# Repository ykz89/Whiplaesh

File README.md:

# Whiplaesh
Inspired by Aespa's latest single '[Whiplash](https://www.youtube.com/watch?v=jWQx2f-CErU)'.

This is a 32 (23333+2) key wireless keyboard featuring:

- Nice!Nano (or alike) controller
- Hotswap or direct solder support for choc, gateron low profile, and MX switches
- Battery through holes for soldering a JST connector or direct wire
- On/off switch
- Reset switch
- VIK connector

## Case
Todo

## Build guide
Todo

## Firmware
Todo

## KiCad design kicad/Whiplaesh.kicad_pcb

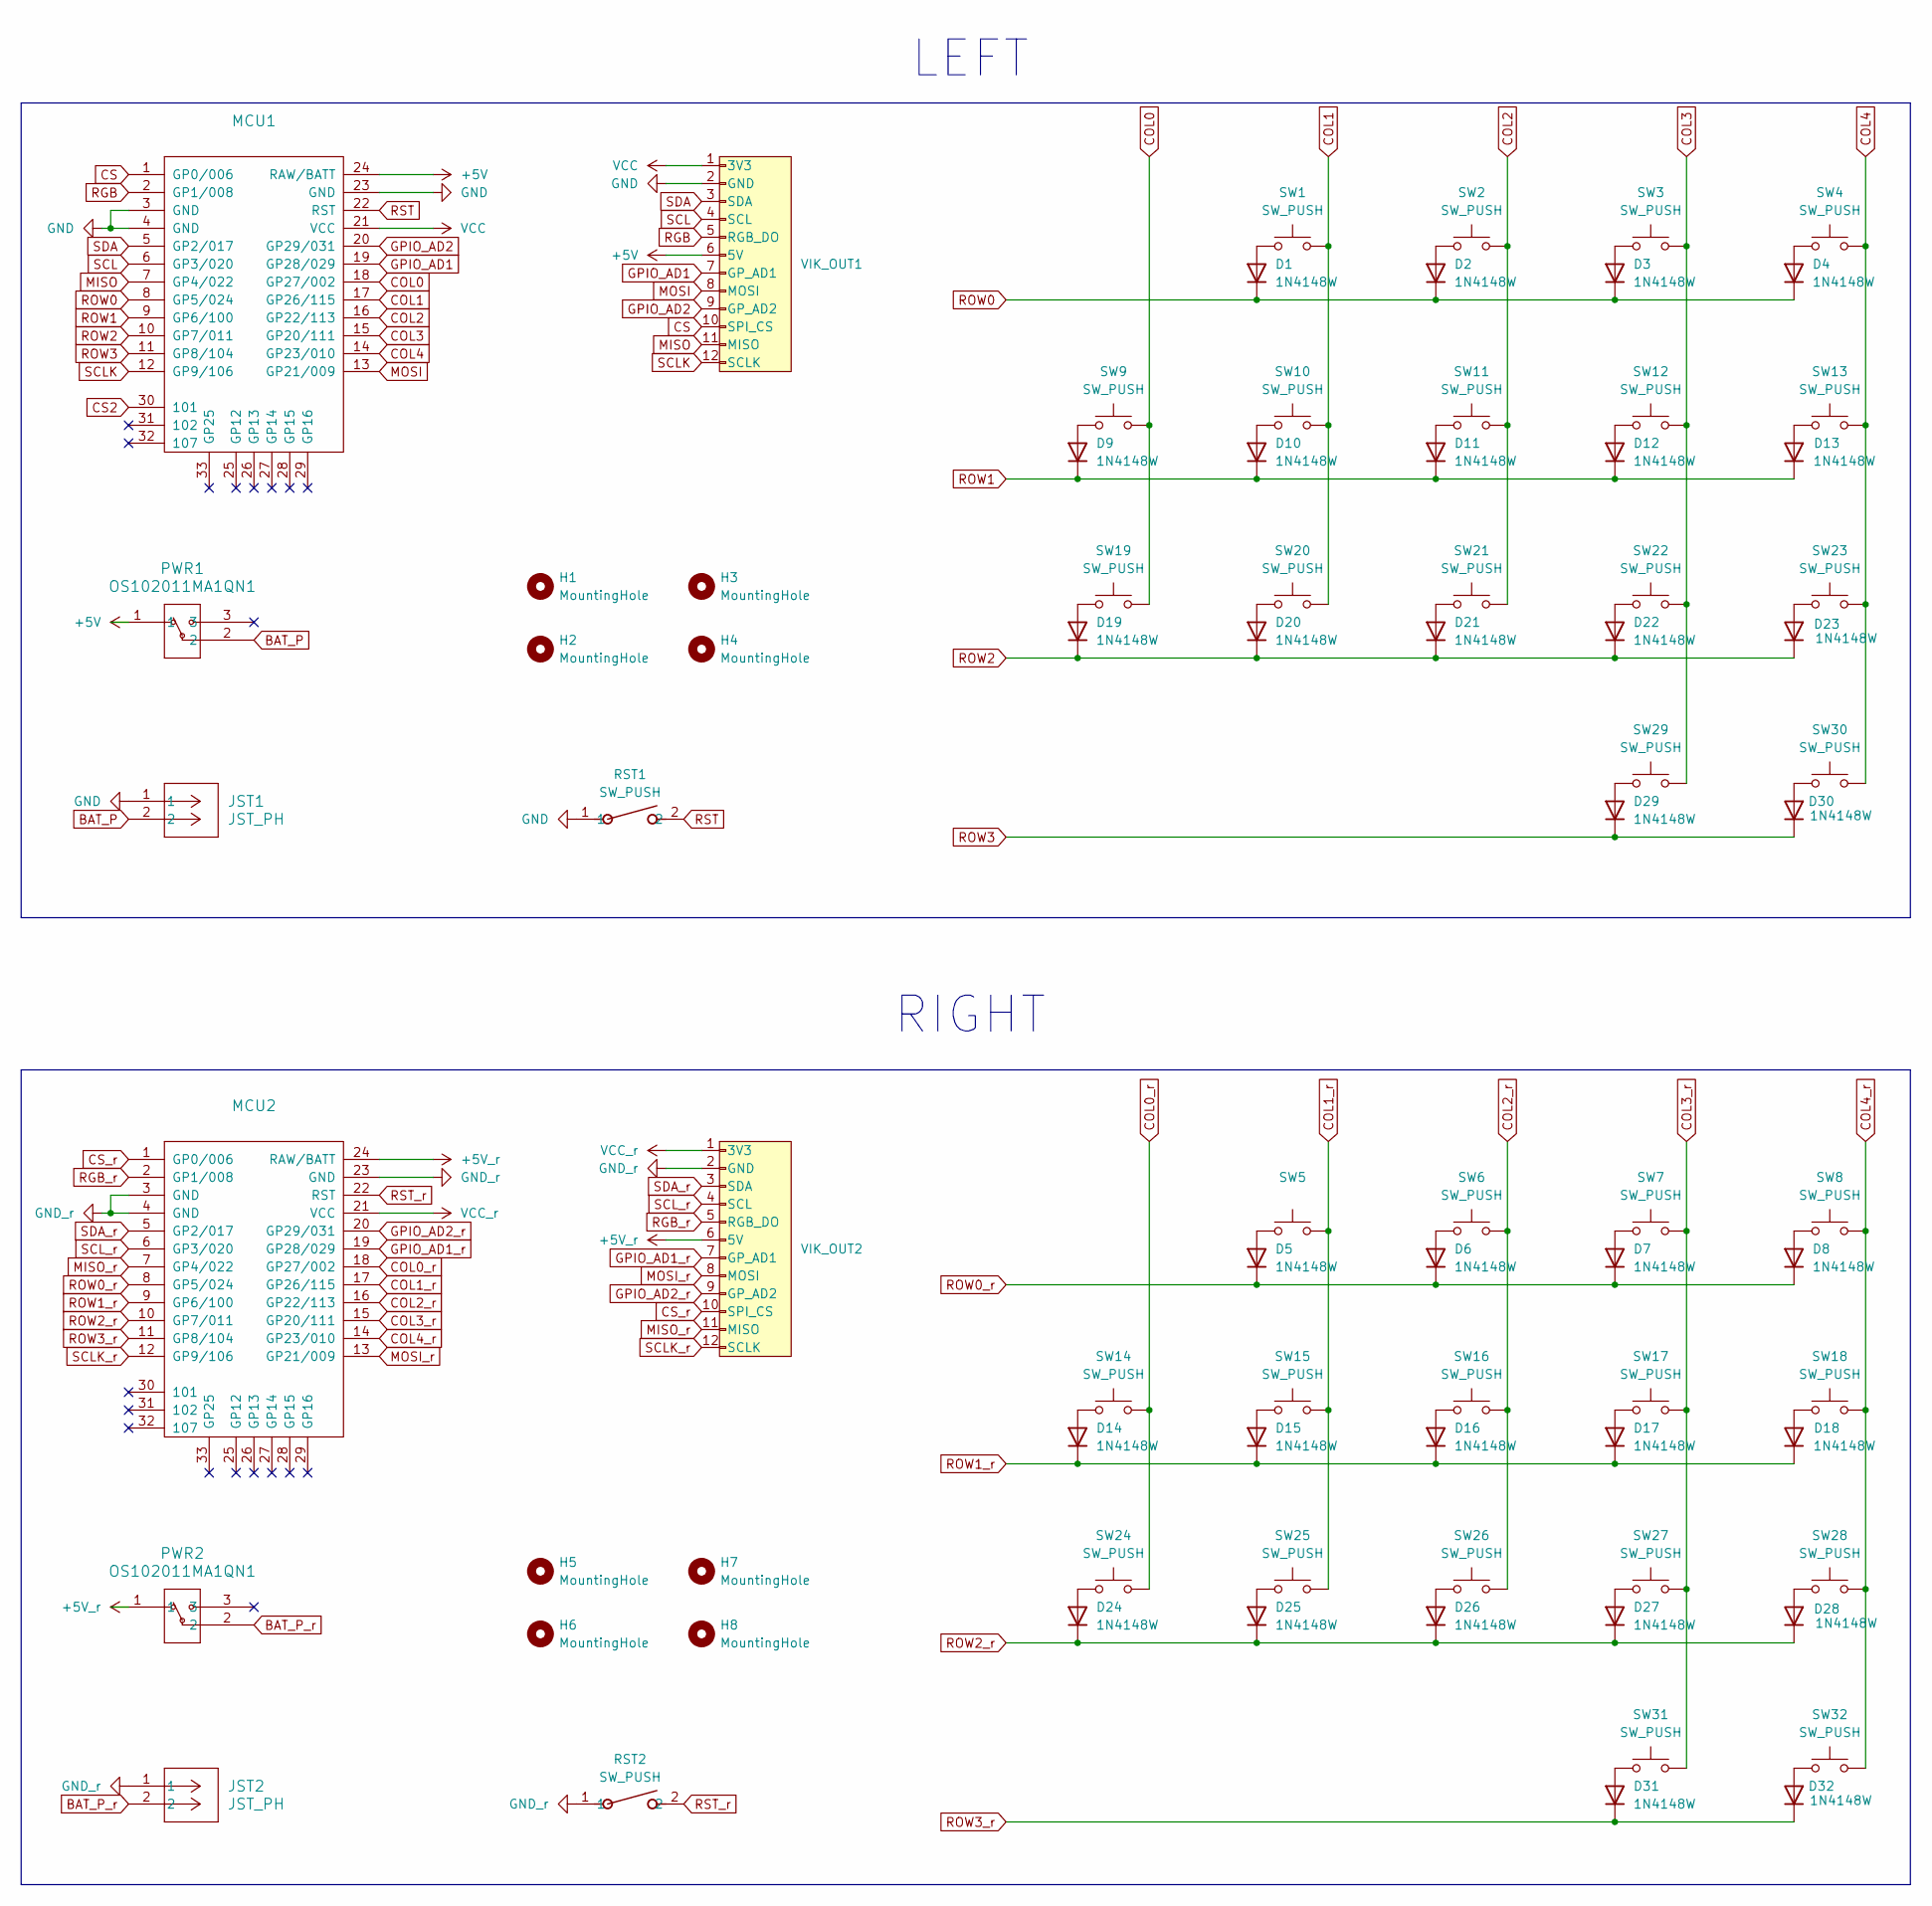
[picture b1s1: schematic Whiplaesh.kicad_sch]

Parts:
D1, D2, D3, D4, D5, D6, D7, D8, D9, D10, D11, D12, D13, D14, D15, D16, D17, D18, D19, D20, D21, D22, D23, D24, D25, D26, D27, D28, D29, D30, D31, D32: 1N4148W; D3_TH_SMD
H1, H2, H3, H4, H5, H6, H7, H8: MountingHole; MountingHole_2.2mm_M2
JST1, JST2: JST_PH; JST_PH_S2B-PH-K_1x02_P2.00mm_Horizontal
MCU1, MCU2: ArduinoProMicro
PWR1, PWR2: OS102011MA1QN1; OS102011MA1QN1_CNK
RST1, RST2: SW_PUSH; SW_SKHLACA010_ALPS
SW1, SW2, SW3, SW4, SW5, SW6, SW7, SW8, SW9, SW10, SW11, SW12, SW13, SW14, SW15, SW16, SW17, SW18, SW19, SW20, SW21, SW22, SW23, SW24, SW25, SW26, SW27, SW28, SW29, SW30, SW31, SW32: SW_PUSH; gateron-ks27-choc-v1-mx-soldered-and-hotswap
VIK_OUT1, VIK_OUT2: vik-keyboard-connector-horizontal

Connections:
+5V: MCU1.24 (RAW/BATT), PWR1.1, VIK_OUT1.6 (5V)
+5V_r: MCU2.24 (RAW/BATT), PWR2.1, VIK_OUT2.6 (5V)
BAT_P: JST1.2, PWR1.2
BAT_P_r: JST2.2, PWR2.2
COL0: MCU1.18 (GP27/002), SW9.2, SW19.2
COL0_r: MCU2.18 (GP27/002), SW14.2, SW24.2
COL1: MCU1.17 (GP26/115), SW1.2, SW10.2, SW20.2
COL1_r: MCU2.17 (GP26/115), SW5.2, SW15.2, SW25.2
COL2: MCU1.16 (GP22/113), SW2.2, SW11.2, SW21.2
COL2_r: MCU2.16 (GP22/113), SW6.2, SW16.2, SW26.2
COL3: MCU1.15 (GP20/111), SW3.2, SW12.2, SW22.2, SW29.2
COL3_r: MCU2.15 (GP20/111), SW7.2, SW17.2, SW27.2, SW31.2
COL4: MCU1.14 (GP23/010), SW4.2, SW13.2, SW23.2, SW30.2
COL4_r: MCU2.14 (GP23/010), SW8.2, SW18.2, SW28.2, SW32.2
CS: MCU1.1 (GP0/006), VIK_OUT1.10 (SPI_CS)
CS_r: MCU2.1 (GP0/006), VIK_OUT2.10 (SPI_CS)
GND: JST1.1, MCU1.3 (GND), MCU1.4 (GND), MCU1.23 (GND), RST1.1, VIK_OUT1.2 (GND)
GND_r: JST2.1, MCU2.3 (GND), MCU2.4 (GND), MCU2.23 (GND), RST2.1, VIK_OUT2.2 (GND)
GPIO_AD1: MCU1.19 (GP28/029), VIK_OUT1.7 (GP_AD1)
GPIO_AD1_r: MCU2.19 (GP28/029), VIK_OUT2.7 (GP_AD1)
GPIO_AD2: MCU1.20 (GP29/031), VIK_OUT1.9 (GP_AD2)
GPIO_AD2_r: MCU2.20 (GP29/031), VIK_OUT2.9 (GP_AD2)
MISO: MCU1.7 (GP4/022), VIK_OUT1.11 (MISO)
MISO_r: MCU2.7 (GP4/022), VIK_OUT2.11 (MISO)
MOSI: MCU1.13 (GP21/009), VIK_OUT1.8 (MOSI)
MOSI_r: MCU2.13 (GP21/009), VIK_OUT2.8 (MOSI)
unnamed: D1.2 (A), SW1.1
unnamed: D2.2 (A), SW2.1
unnamed: D3.2 (A), SW3.1
unnamed: D4.2 (A), SW4.1
unnamed: D5.2 (A), SW5.1
unnamed: D6.2 (A), SW6.1
unnamed: D7.2 (A), SW7.1
unnamed: D8.2 (A), SW8.1
unnamed: D9.2 (A), SW9.1
unnamed: D10.2 (A), SW10.1
unnamed: D11.2 (A), SW11.1
unnamed: D12.2 (A), SW12.1
unnamed: D13.2 (A), SW13.1
unnamed: D14.2 (A), SW14.1
unnamed: D15.2 (A), SW15.1
unnamed: D16.2 (A), SW16.1
unnamed: D17.2 (A), SW17.1
unnamed: D18.2 (A), SW18.1
unnamed: D19.2 (A), SW19.1
unnamed: D20.2 (A), SW20.1
unnamed: D21.2 (A), SW21.1
unnamed: D22.2 (A), SW22.1
unnamed: D23.2 (A), SW23.1
unnamed: D24.2 (A), SW24.1
unnamed: D25.2 (A), SW25.1
unnamed: D26.2 (A), SW26.1
unnamed: D27.2 (A), SW27.1
unnamed: D28.2 (A), SW28.1
unnamed: D29.2 (A), SW29.1
unnamed: D30.2 (A), SW30.1
unnamed: D31.2 (A), SW31.1
unnamed: D32.2 (A), SW32.1
RGB: MCU1.2 (GP1/008), VIK_OUT1.5 (RGB_DO)
RGB_r: MCU2.2 (GP1/008), VIK_OUT2.5 (RGB_DO)
ROW0: D1.1 (K), D2.1 (K), D3.1 (K), D4.1 (K), MCU1.8 (GP5/024)
ROW0_r: D5.1 (K), D6.1 (K), D7.1 (K), D8.1 (K), MCU2.8 (GP5/024)
ROW1: D9.1 (K), D10.1 (K), D11.1 (K), D12.1 (K), D13.1 (K), MCU1.9 (GP6/100)
ROW1_r: D14.1 (K), D15.1 (K), D16.1 (K), D17.1 (K), D18.1 (K), MCU2.9 (GP6/100)
ROW2: D19.1 (K), D20.1 (K), D21.1 (K), D22.1 (K), D23.1 (K), MCU1.10 (GP7/011)
ROW2_r: D24.1 (K), D25.1 (K), D26.1 (K), D27.1 (K), D28.1 (K), MCU2.10 (GP7/011)
ROW3: D29.1 (K), D30.1 (K), MCU1.11 (GP8/104)
ROW3_r: D31.1 (K), D32.1 (K), MCU2.11 (GP8/104)
RST: MCU1.22 (RST), RST1.2
RST_r: MCU2.22 (RST), RST2.2
SCL: MCU1.6 (GP3/020), VIK_OUT1.4 (SCL)
SCLK: MCU1.12 (GP9/106), VIK_OUT1.12 (SCLK)
SCLK_r: MCU2.12 (GP9/106), VIK_OUT2.12 (SCLK)
SCL_r: MCU2.6 (GP3/020), VIK_OUT2.4 (SCL)
SDA: MCU1.5 (GP2/017), VIK_OUT1.3 (SDA)
SDA_r: MCU2.5 (GP2/017), VIK_OUT2.3 (SDA)
VCC: MCU1.21 (VCC), VIK_OUT1.1 (3V3)
VCC_r: MCU2.21 (VCC), VIK_OUT2.1 (3V3)

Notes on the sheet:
LEFT
RIGHT

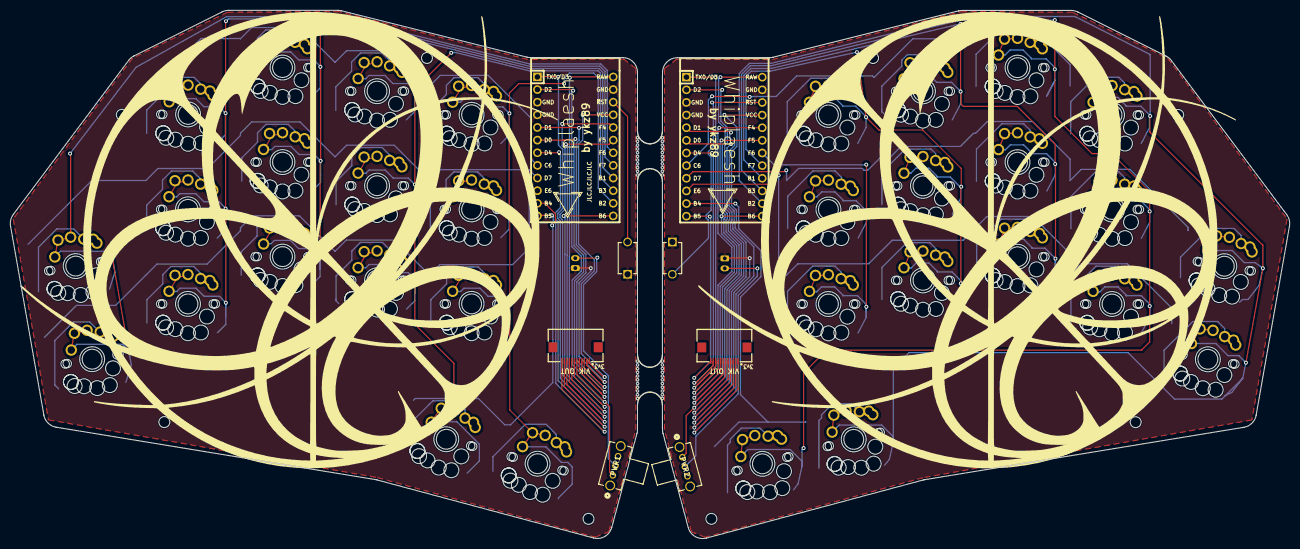
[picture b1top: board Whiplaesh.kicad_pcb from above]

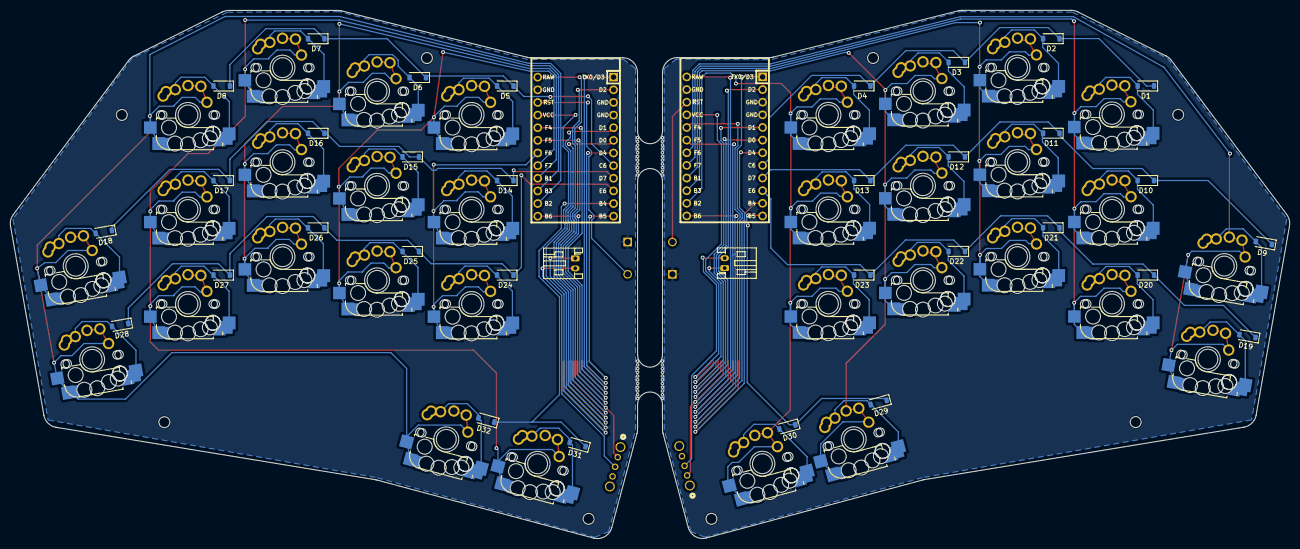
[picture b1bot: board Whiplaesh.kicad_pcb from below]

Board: 2 copper layers, 257.1 x 106.2 mm, 84 parts (34 on the bottom side), 78 nets.

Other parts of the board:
mouse-bite-5mm-slot, mouse-bite-5mm-slot#2: VAL**; mouse-bite-5mm-slot

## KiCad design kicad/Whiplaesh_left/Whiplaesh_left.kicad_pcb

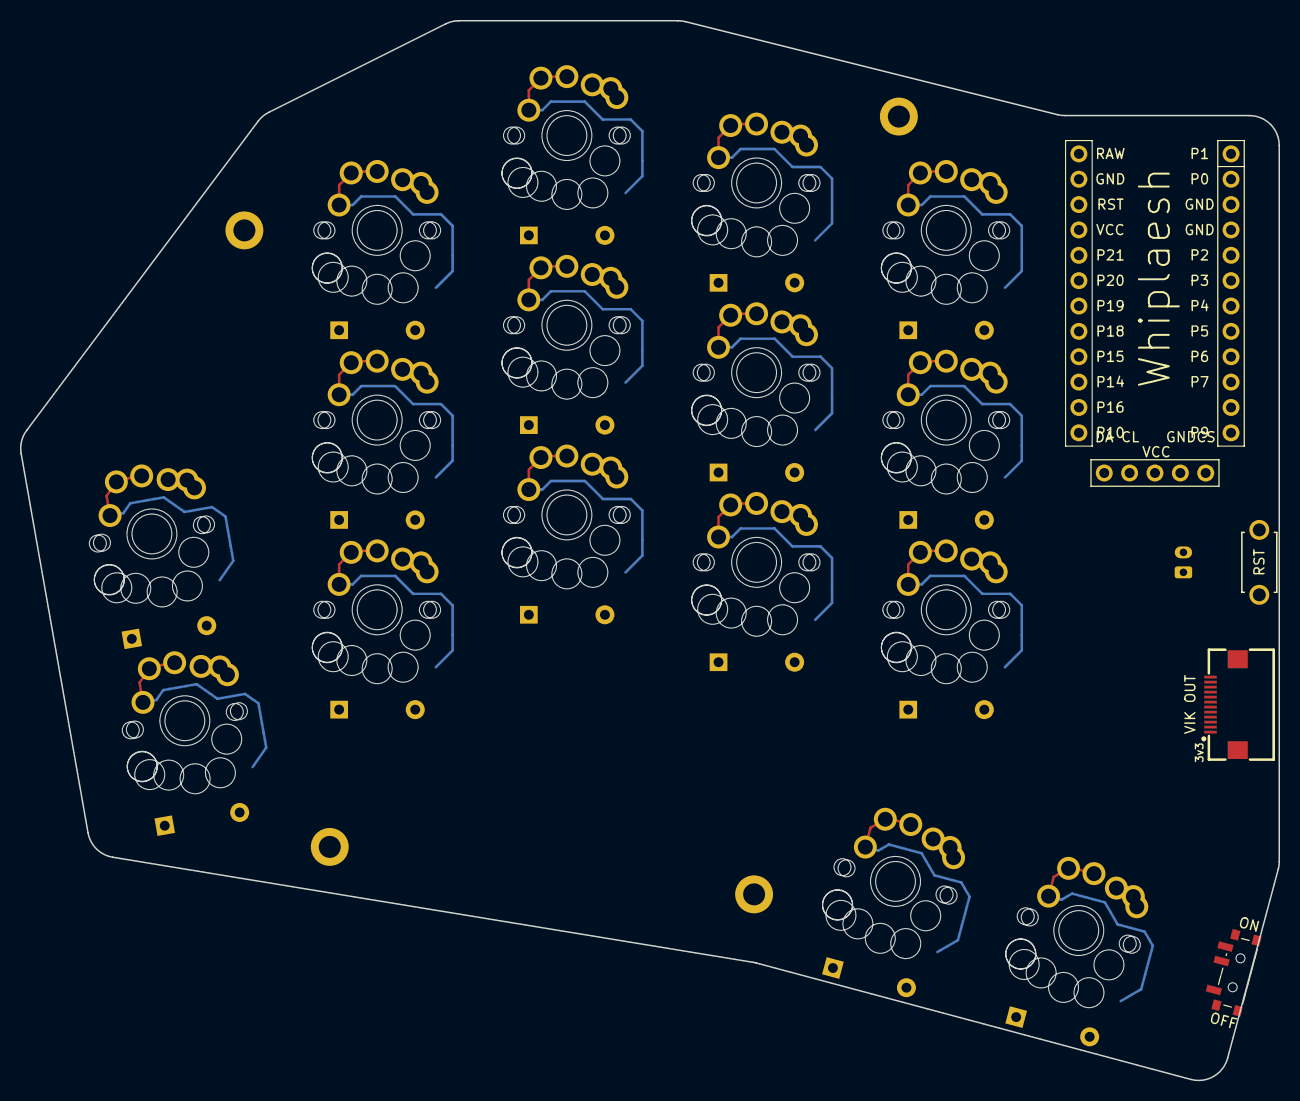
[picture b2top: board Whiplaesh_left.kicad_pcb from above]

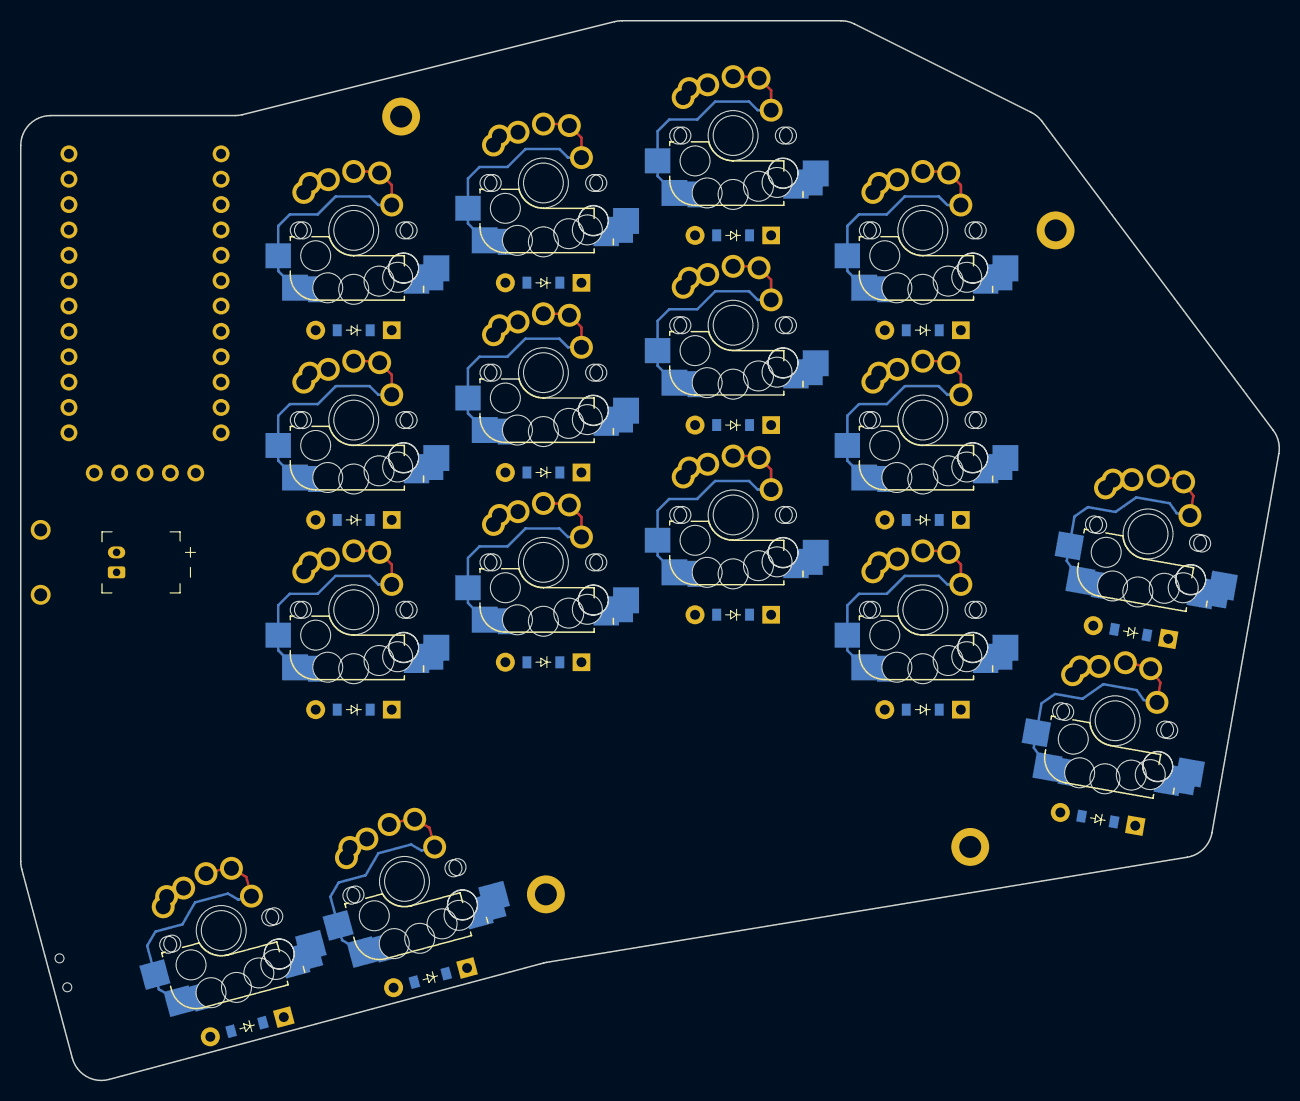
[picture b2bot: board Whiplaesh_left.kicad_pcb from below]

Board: 2 copper layers, 126.1 x 106.1 mm, 42 parts (33 on the bottom side), 38 nets.

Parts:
D1, D2, D3, D4, D5, D6, D7, D8, D9, D10, D11, D12, D13, D14, D15, D16: diode_tht_sod123
DISP1: display_nice_view
H1, H2, H3, H4: mounting_hole_plated
JST1: battery_connector_jst_ph_2
MCU1: mcu_nice_nano
PWR1: power_switch_smd_side
RST1: reset_switch_tht_top
SW1, SW2, SW3, SW4, SW5, SW6, SW7, SW8, SW9, SW10, SW11, SW12, SW13, SW14, SW15, SW16: ks27-choc-v1-mx-soldered-and-hotswap
VIK_OUT1: vik-keyboard-connector-horizontal

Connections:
BAT_P: JST1.2, PWR1.3
GND: DISP1.2, JST1.1, MCU1.3, MCU1.4, MCU1.23, RST1.2, VIK_OUT1.2
P0: MCU1.2, VIK_OUT1.5
P1: MCU1.1, VIK_OUT1.10
P2: MCU1.5, VIK_OUT1.3
P3: MCU1.6, VIK_OUT1.4
P4: D5.1, D8.1, D11.1, D14.1, MCU1.7, VIK_OUT1.11
P5: D2.1, D4.1, D7.1, D10.1, D13.1, MCU1.8
P6: D1.1, D3.1, D6.1, D9.1, D12.1, MCU1.9
P8: D15.1, D16.1, MCU1.11
P9: DISP1.4, MCU1.12, VIK_OUT1.12
P10: DISP1.5, MCU1.13, VIK_OUT1.8
P14: MCU1.15, SW9.1, SW10.1, SW11.1, SW15.1
P15: MCU1.16, SW6.1, SW7.1, SW8.1
P16: MCU1.14, SW12.1, SW13.1, SW14.1, SW16.1
P18: MCU1.17, SW3.1, SW4.1, SW5.1
P19: MCU1.18, SW1.1, SW2.1
P20: MCU1.19, VIK_OUT1.9
P21: MCU1.20, VIK_OUT1.7
RAW: MCU1.24, PWR1.2, VIK_OUT1.6
RST: MCU1.22, RST1.1
VCC: DISP1.3, MCU1.21, VIK_OUT1.1
index_bottom: D9.2, SW9.2
index_home: D10.2, SW10.2
index_top: D11.2, SW11.2
inner_bottom: D12.2, SW12.2
inner_home: D13.2, SW13.2
inner_top: D14.2, SW14.2
left_cluster: D15.2, SW15.2
middle_bottom: D6.2, SW6.2
middle_home: D7.2, SW7.2
middle_top: D8.2, SW8.2
pinky_bottom: D1.2, SW1.2
pinky_home: D2.2, SW2.2
right_cluster: D16.2, SW16.2
ring_bottom: D3.2, SW3.2
ring_home: D4.2, SW4.2
ring_top: D5.2, SW5.2

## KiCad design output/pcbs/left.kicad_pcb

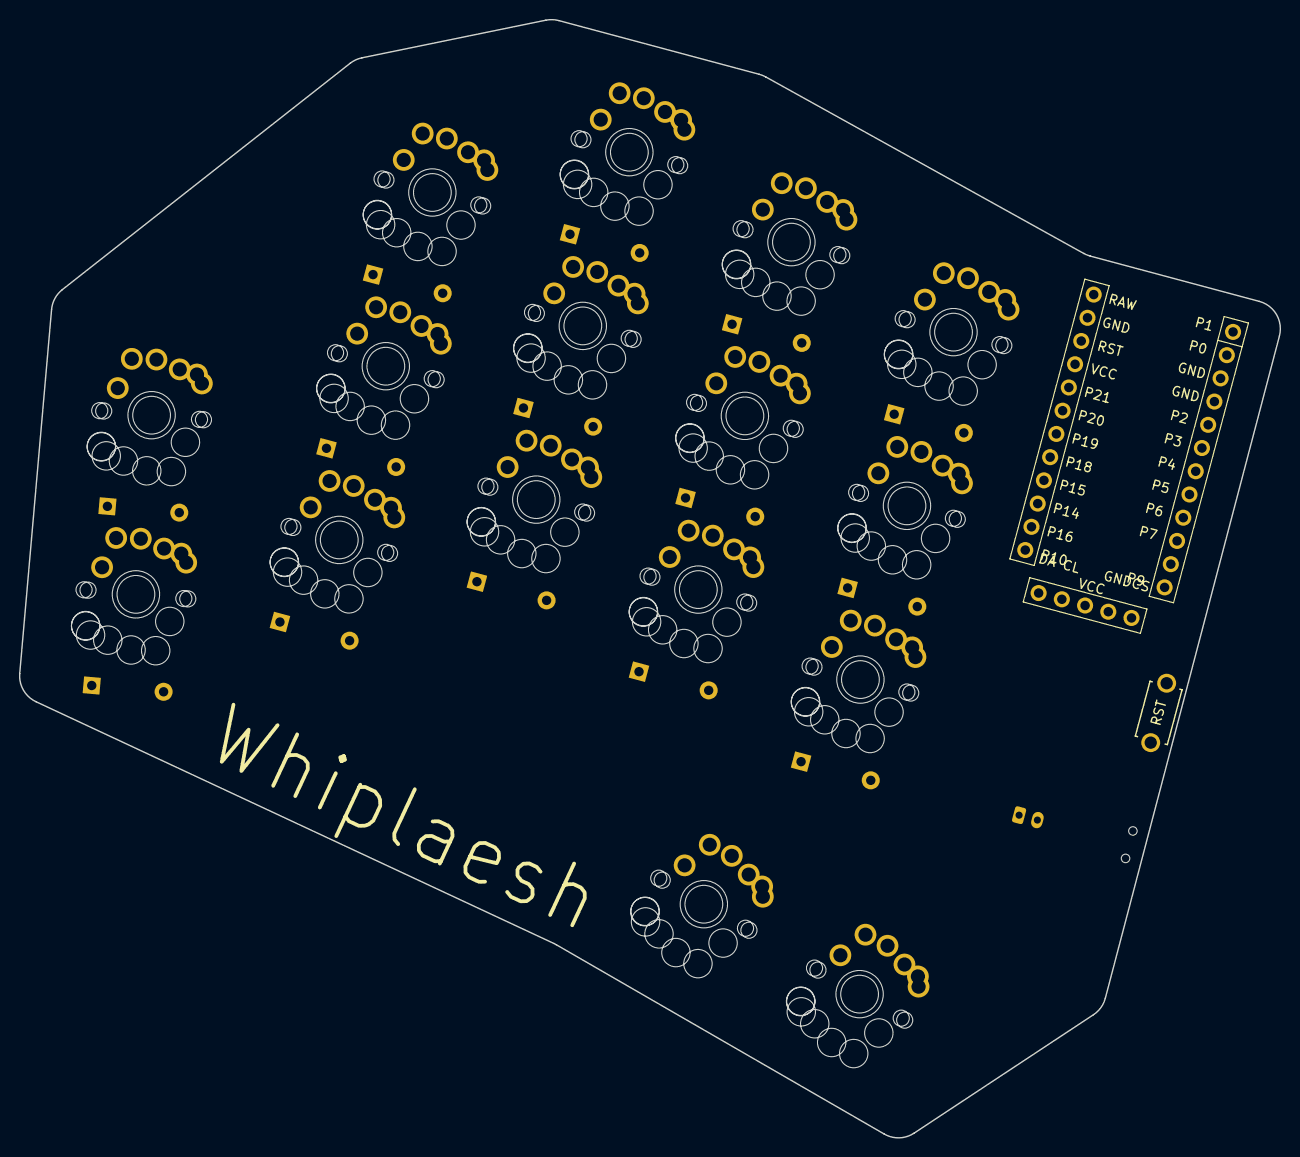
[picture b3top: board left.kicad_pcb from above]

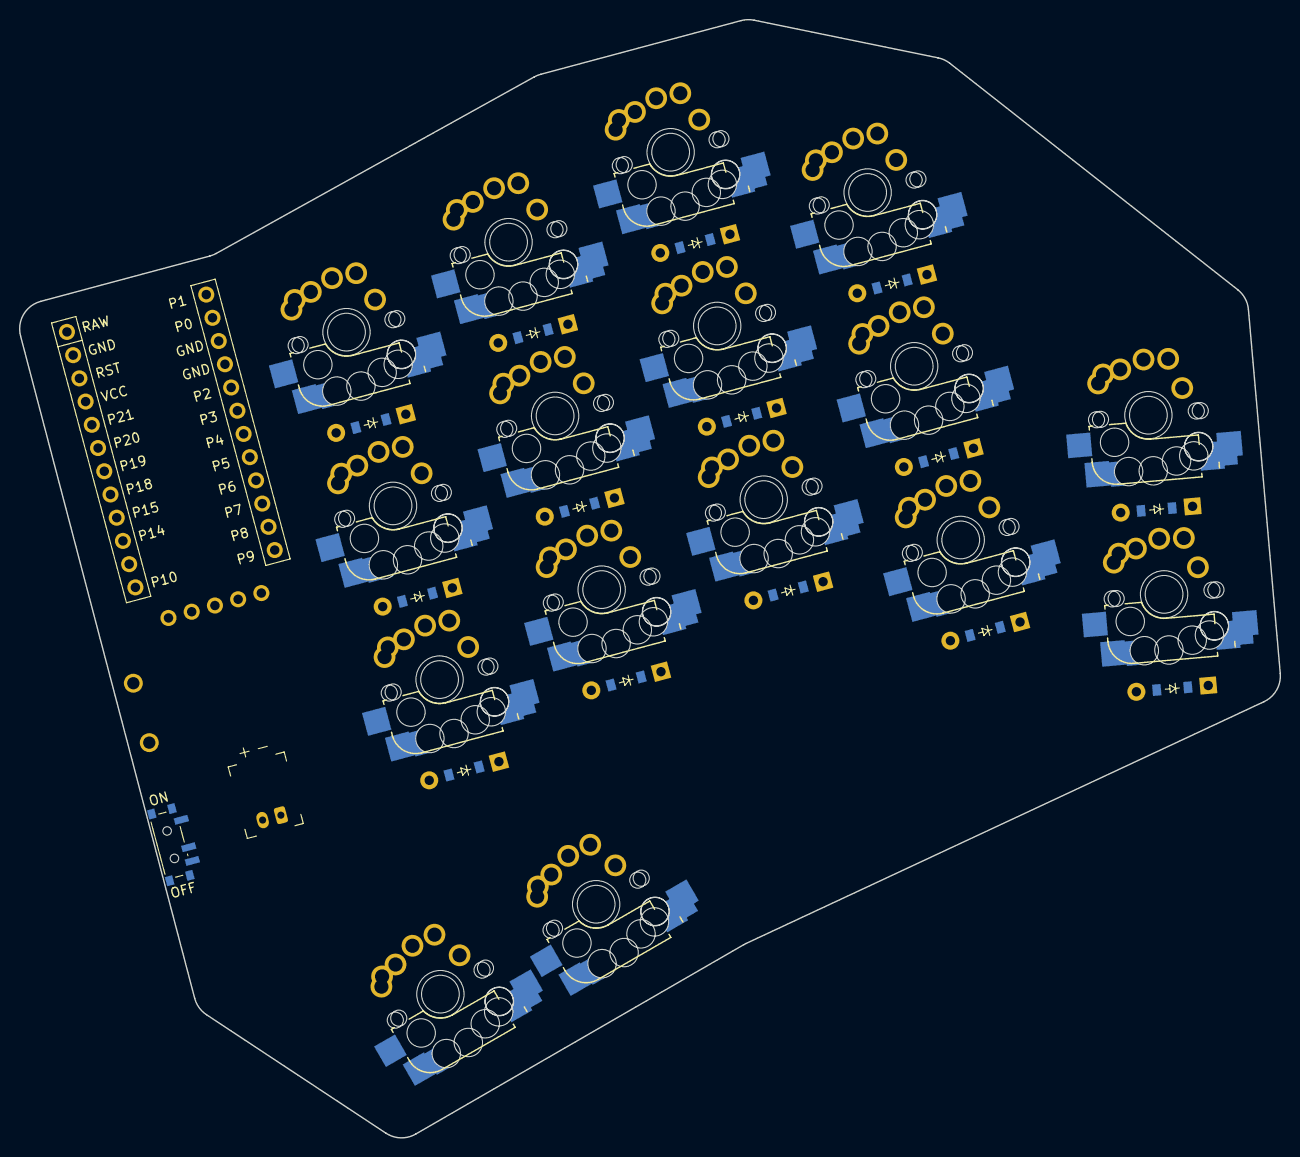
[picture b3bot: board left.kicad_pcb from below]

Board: 2 copper layers, 133.2 x 118.1 mm, 35 parts (16 on the bottom side), 18 nets, no tracks yet.

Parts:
D1, D2, D3, D4, D5, D6, D7, D8, D9, D10, D11, D12, D13, D14: diode_tht_sod123
DISP1: display_nice_view
JST1: battery_connector_jst_ph_2
MCU1: mcu_nice_nano
PWR1: power_switch_smd_side
RST1: reset_switch_tht_top
S1, S2, S3, S4, S5, S6, S7, S8, S9, S10, S11, S12, S13, S14, S15, S16: ks27-choc-v1-mx-soldered-and-hotswap

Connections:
BAT_P: JST1.2, PWR1.1
GND: JST1.1, MCU1.3, MCU1.4, MCU1.23, RST1.2
RAW: MCU1.24, PWR1.2
RST: MCU1.22, RST1.1
index_bottom: D9.2, S9.2
index_home: D10.2, S10.2
index_top: D11.2, S11.2
inner_bottom: D12.2, S12.2
inner_home: D13.2, S13.2
inner_top: D14.2, S14.2
middle_bottom: D6.2, S6.2
middle_home: D7.2, S7.2
middle_top: D8.2, S8.2
pinky_bottom: D1.2, S1.2
pinky_home: D2.2, S2.2
ring_bottom: D3.2, S3.2
ring_home: D4.2, S4.2
ring_top: D5.2, S5.2

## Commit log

2024-10-26 Add keyswitch footprint
2024-10-26 Add footprints
2024-10-27 Fix and add switch footprint
2024-10-27 Update thumbs and add nets
2024-10-27 Add gitignore
2024-10-28 Add traces to switch footprint
2024-10-30 Move ergogen footprints to separate repo, Make schematics
2024-10-30 Add missing connections, fix diodes references, fix shared pins on vik connector
2024-10-31 Separate left and right, add kicad footprints and symbols
2024-11-01 add right board in ergogen config
2024-11-03 Remove nice!view and update schematics and pcb
2024-11-04 Redo routing, add ground plane, add fingerpunch footprints
2024-11-04 Fix silkscreen, add production files
2024-11-04 Tentatively add bottom plate
2024-11-04 Mirror ground fill, fix battery connector position
2024-11-04 Fix dangling traces and references
2024-11-04 Create LICENSE
2024-11-13 Add missing trace
